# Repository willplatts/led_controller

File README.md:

# led_controller
LED array PCB for lighting with daisy chain controller

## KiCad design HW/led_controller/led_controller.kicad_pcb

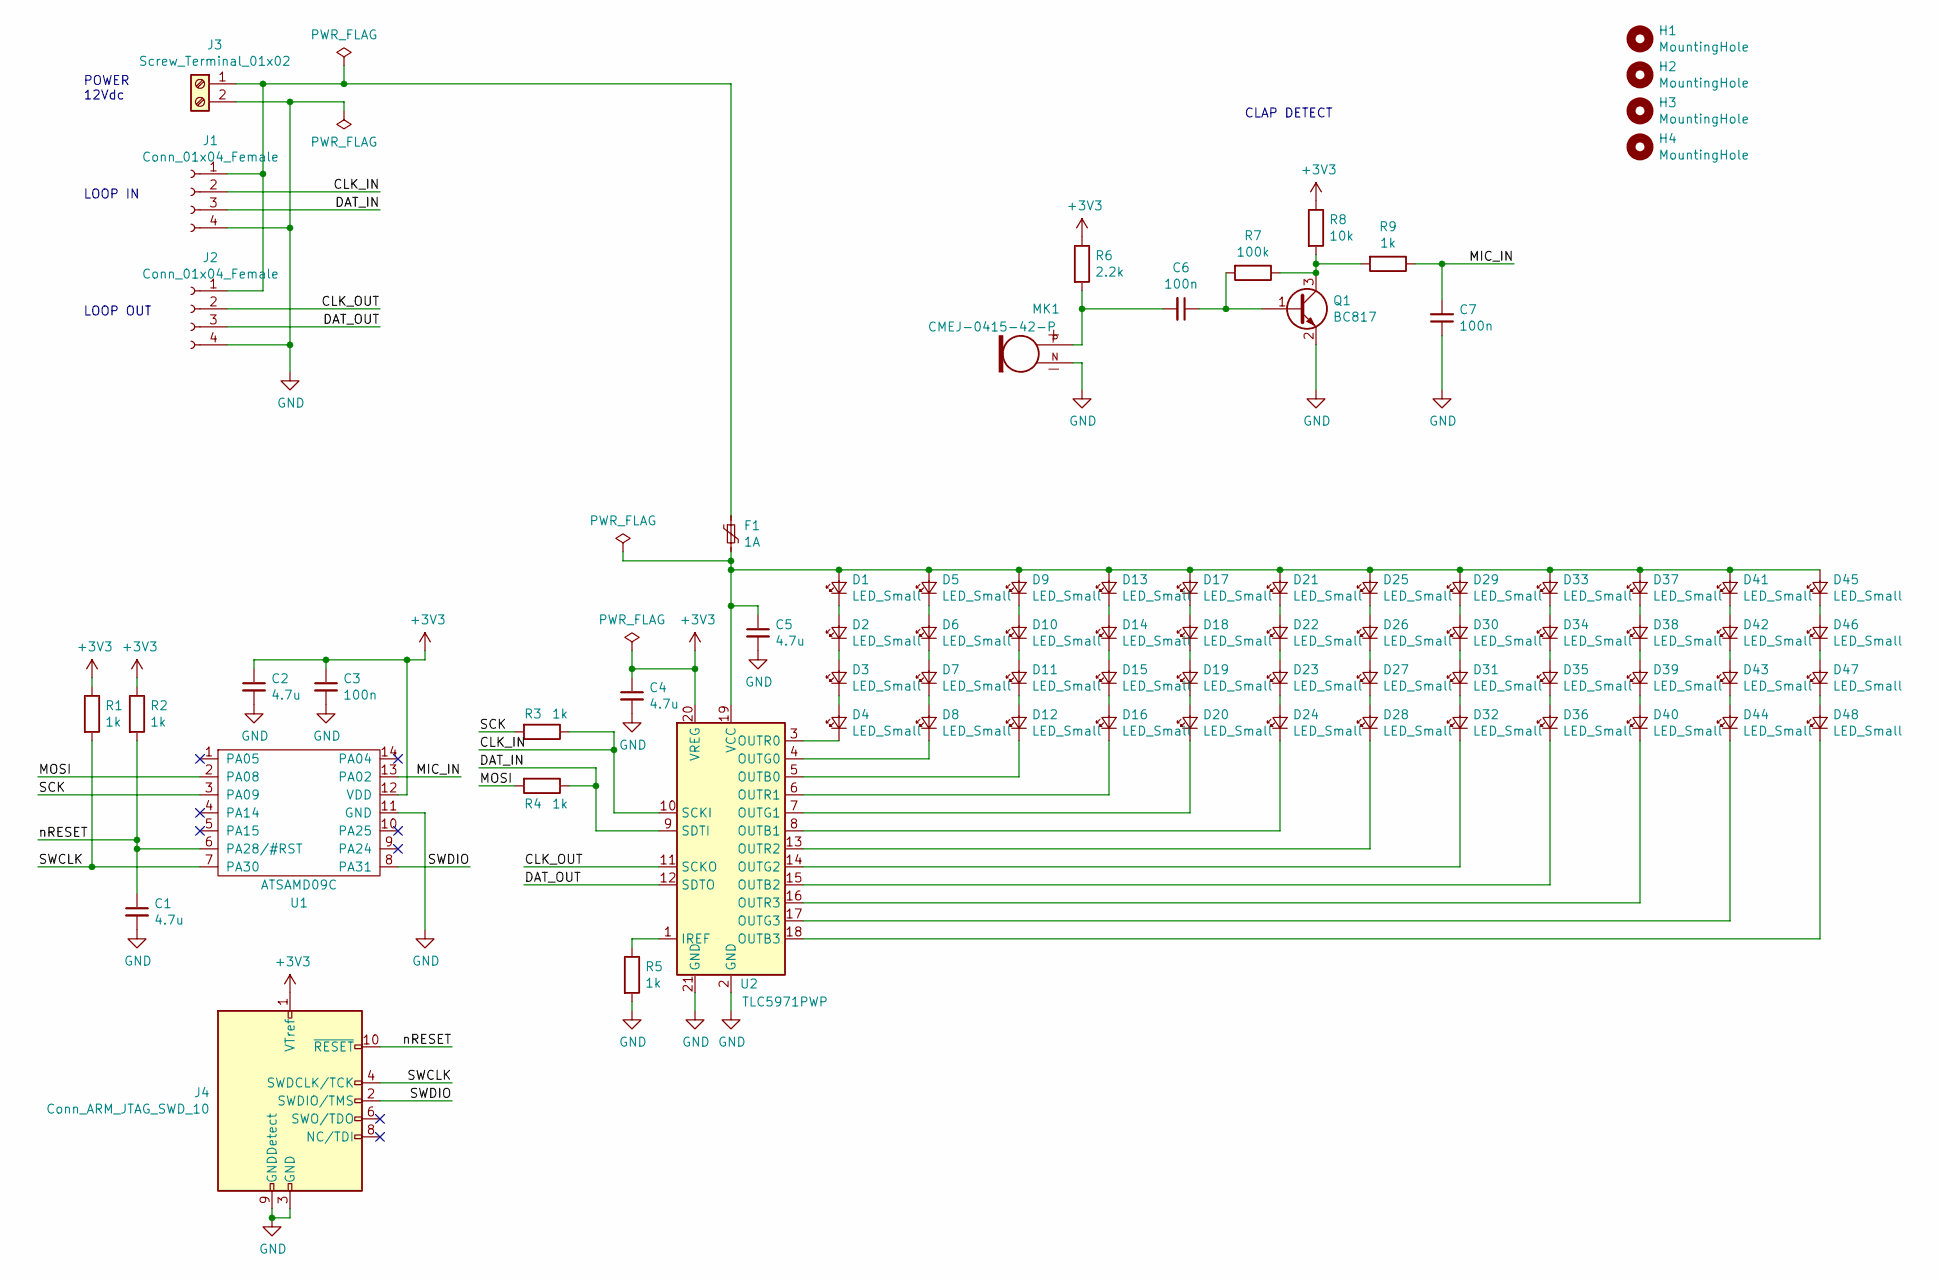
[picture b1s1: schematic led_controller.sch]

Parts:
C1, C2, C4, C5: 4.7u; C_1206_3216Metric_Pad1.42x1.75mm_HandSolder
C3, C6, C7: 100n; C_0603_1608Metric_Pad1.05x0.95mm_HandSolder
D1, D2, D3, D4, D5, D6, D7, D8, D9, D10, D11, D12, D13, D14, D15, D16, D17, D18, D19, D20, D21, D22, D23, D24, D25, D26, D27, D28, D29, D30, D31, D32, D33, D34, D35, D36, D37, D38, D39, D40, D41, D42, D43, D44, D45, D46, D47, D48: LED_Small; LED_PLCC_2835_Handsoldering
F1: 1A; R_1206_3216Metric_Pad1.42x1.75mm_HandSolder
H1, H2, H3, H4: MountingHole; MountingHole_3.2mm_M3
J1, J2: Conn_01x04_Female; PinHeader_1x04_P2.54mm_Vertical
J3: Screw_Terminal_01x02; TerminalBlock_Phoenix_MKDS-1,5-2_1x02_P5.00mm_Horizontal
J4: Conn_ARM_JTAG_SWD_10; PinHeader_2x05_P1.27mm_Vertical
MK1: CMEJ-0415-42-P; MIC_CMEJ-0415-42-P
Q1: BC817; SOT-23
R1, R2, R3, R4, R5, R9: 1k; R_0603_1608Metric_Pad1.05x0.95mm_HandSolder
R6: 2.2k; R_0603_1608Metric_Pad1.05x0.95mm_HandSolder
R7: 100k; R_0603_1608Metric_Pad1.05x0.95mm_HandSolder
R8: 10k; R_0603_1608Metric_Pad1.05x0.95mm_HandSolder
U1: ATSAMD09C; SOIC-14_3.9x8.7mm_P1.27mm
U2: TLC5971PWP; HTSSOP-20-1EP_4.4x6.5mm_P0.65mm_EP3.4x6.5mm_Mask2.75x3.43mm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

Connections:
+3V3: C2.1, C3.1, C4.1, J4.1 (VTref), R1.1, R2.1, R6.1, R8.1, U1.12 (VDD), U2.20 (VREG)
/CLK_IN: J1.2, R3.1, U2.10 (SCKI)
/CLK_OUT: J2.2, U2.11 (SCKO)
/DAT_IN: J1.3, R4.1, U2.9 (SDTI)
/DAT_OUT: J2.3, U2.12 (SDTO)
/MIC_IN: C7.2, R9.1, U1.13 (PA02)
/MOSI: R4.2, U1.2 (PA08)
/SCK: R3.2, U1.3 (PA09)
/SWCLK: J4.4 (SWDCLK/TCK), R1.2, U1.7 (PA30)
/SWDIO: J4.2 (SWDIO/TMS), U1.8 (PA31)
/nRESET: C1.1, J4.10 (~RESET~), R2.2, U1.6 (PA28/#RST)
GND: C1.2, C2.2, C3.2, C4.2, C5.2, C7.1, J1.4, J2.4, J3.2, J4.3 (GND), J4.5 (GND), J4.9 (GNDDetect), MK1.N (GND), Q1.2 (E), R5.2, U1.11 (GND), U2.2 (GND), U2.21 (GND)
unnamed: C5.1, D1.2 (A), D5.2 (A), D9.2 (A), D13.2 (A), D17.2 (A), D21.2 (A), D25.2 (A), D29.2 (A), D33.2 (A), D37.2 (A), D41.2 (A), D45.2 (A), F1.2, U2.19 (VCC)
unnamed: C6.1, Q1.1 (B), R7.2
unnamed: C6.2, MK1.P (OUTPUT), R6.2
unnamed: D1.1 (K), D2.2 (A)
unnamed: D2.1 (K), D3.2 (A)
unnamed: D3.1 (K), D4.2 (A)
unnamed: D4.1 (K), U2.3 (OUTR0)
unnamed: D5.1 (K), D6.2 (A)
unnamed: D6.1 (K), D7.2 (A)
unnamed: D7.1 (K), D8.2 (A)
unnamed: D8.1 (K), U2.4 (OUTG0)
unnamed: D10.1 (K), D11.2 (A)
unnamed: D9.1 (K), D10.2 (A)
unnamed: D11.1 (K), D12.2 (A)
unnamed: D12.1 (K), U2.5 (OUTB0)
unnamed: D13.1 (K), D14.2 (A)
unnamed: D14.1 (K), D15.2 (A)
unnamed: D15.1 (K), D16.2 (A)
unnamed: D16.1 (K), U2.6 (OUTR1)
unnamed: D17.1 (K), D18.2 (A)
unnamed: D18.1 (K), D19.2 (A)
unnamed: D19.1 (K), D20.2 (A)
unnamed: D20.1 (K), U2.7 (OUTG1)
unnamed: D21.1 (K), D22.2 (A)
unnamed: D22.1 (K), D23.2 (A)
unnamed: D23.1 (K), D24.2 (A)
unnamed: D24.1 (K), U2.8 (OUTB1)
unnamed: D25.1 (K), D26.2 (A)
unnamed: D26.1 (K), D27.2 (A)
unnamed: D27.1 (K), D28.2 (A)
unnamed: D28.1 (K), U2.13 (OUTR2)
unnamed: D29.1 (K), D30.2 (A)
unnamed: D30.1 (K), D31.2 (A)
unnamed: D31.1 (K), D32.2 (A)
unnamed: D32.1 (K), U2.14 (OUTG2)
unnamed: D33.1 (K), D34.2 (A)
unnamed: D34.1 (K), D35.2 (A)
unnamed: D35.1 (K), D36.2 (A)
unnamed: D36.1 (K), U2.15 (OUTB2)
unnamed: D37.1 (K), D38.2 (A)
unnamed: D38.1 (K), D39.2 (A)
unnamed: D39.1 (K), D40.2 (A)
unnamed: D40.1 (K), U2.16 (OUTR3)
unnamed: D41.1 (K), D42.2 (A)
unnamed: D42.1 (K), D43.2 (A)
unnamed: D43.1 (K), D44.2 (A)
unnamed: D44.1 (K), U2.17 (OUTG3)
unnamed: D45.1 (K), D46.2 (A)
unnamed: D46.1 (K), D47.2 (A)
unnamed: D47.1 (K), D48.2 (A)
unnamed: D48.1 (K), U2.18 (OUTB3)
unnamed: F1.1, J1.1, J2.1, J3.1
unnamed: Q1.3 (C), R7.1, R8.2, R9.2
unnamed: R5.1, U2.1 (IREF)

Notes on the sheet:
LOOP IN
LOOP OUT
POWER 12Vdc
CLAP DETECT

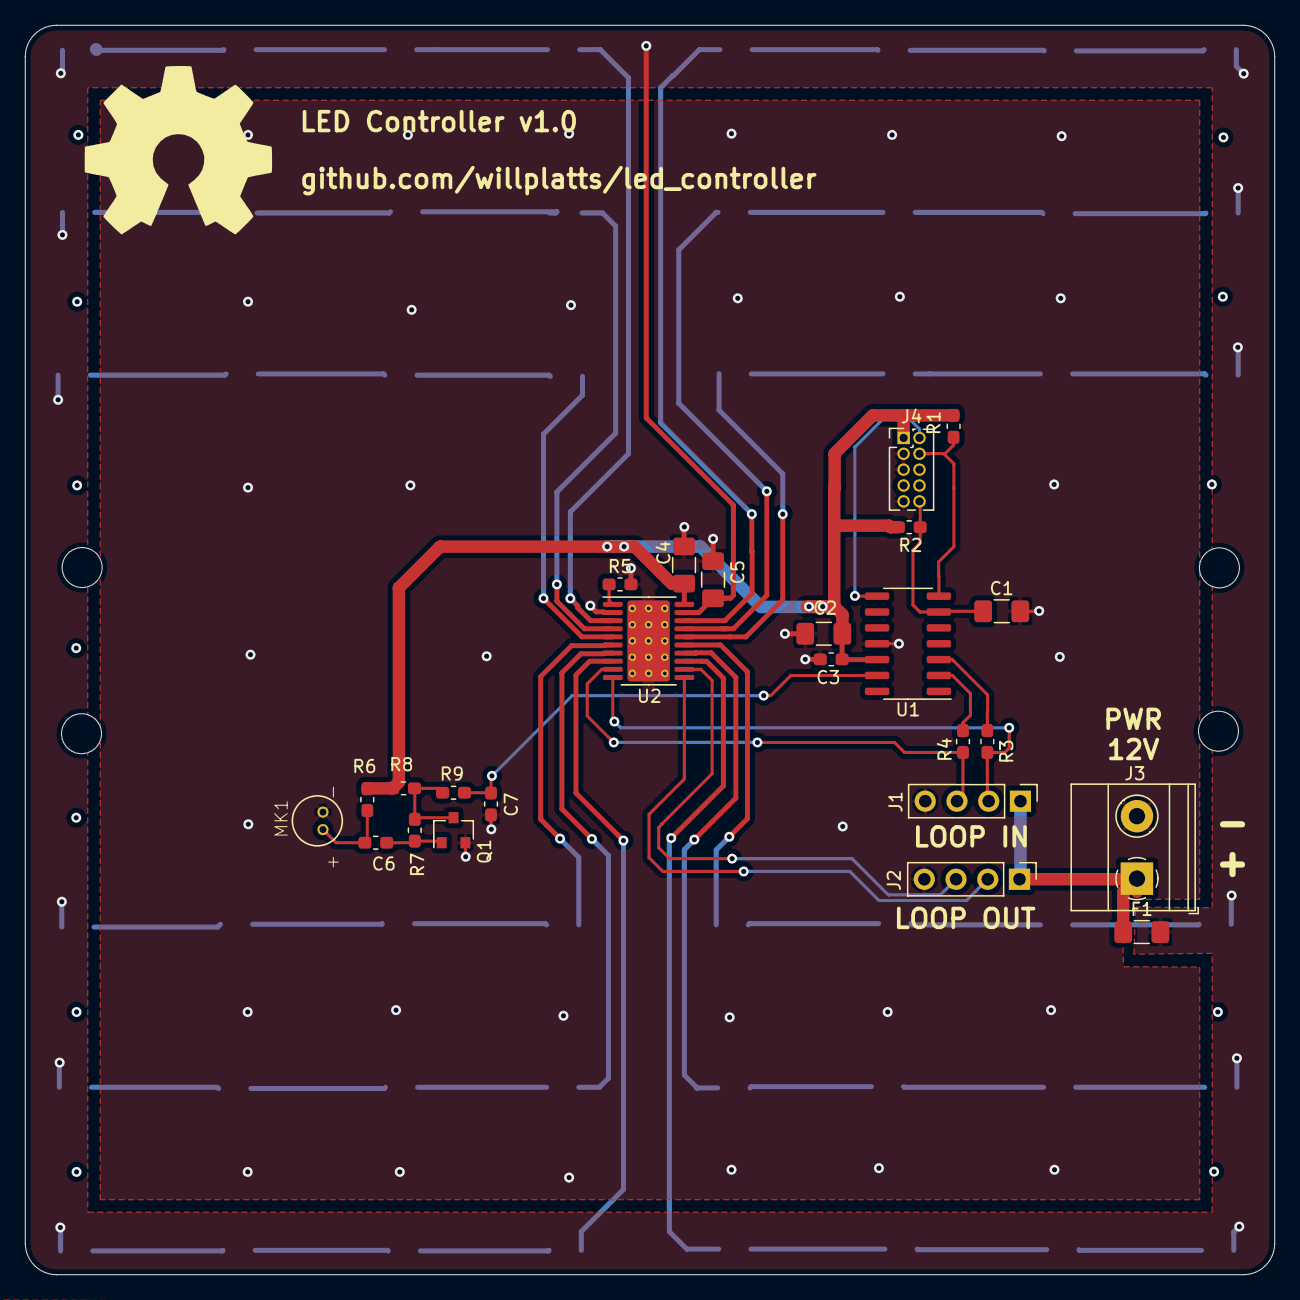
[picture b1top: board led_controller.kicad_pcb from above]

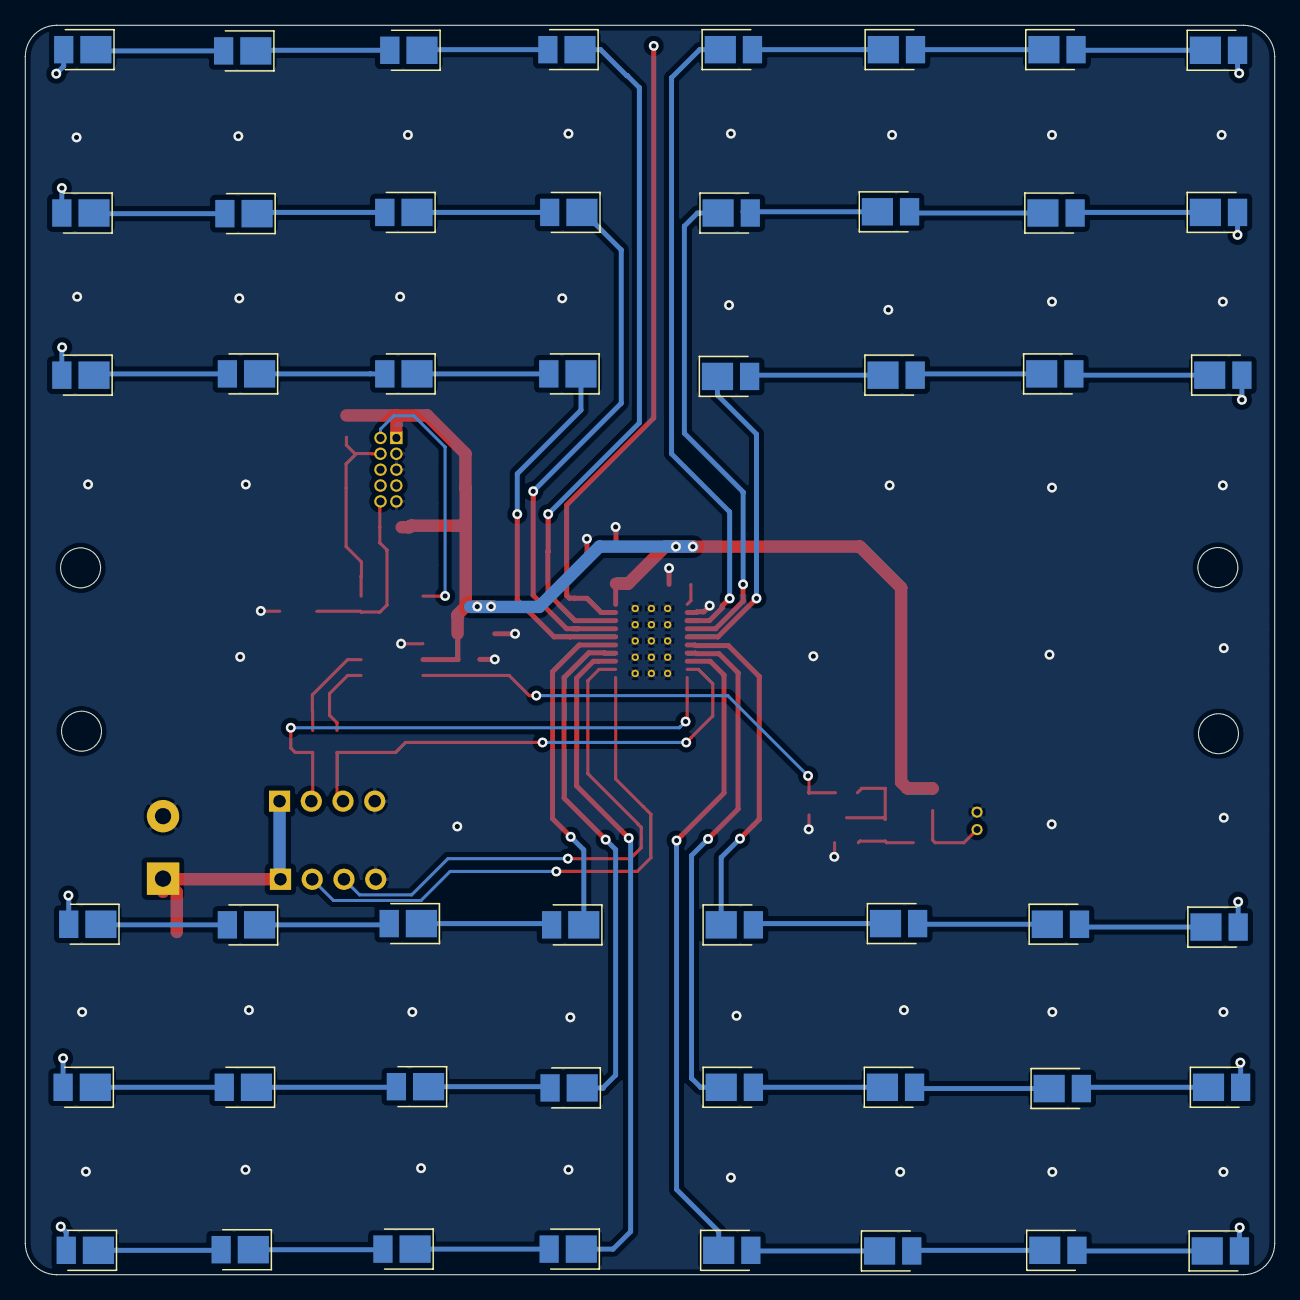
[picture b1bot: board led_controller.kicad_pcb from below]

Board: 2 copper layers, 100.0 x 100.0 mm, 77 parts (48 on the bottom side), 66 nets.

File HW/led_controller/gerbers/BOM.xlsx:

Ref | Value | Part | Manufacturer part no | Supplier | Qty
C1, C2, C4, C5 | 4.7u | Capacitor, 1206, 4.7uF, X5R, 25V | Generic | DIGI 1276-2880-1-ND | 4
C3, C6, C7 | 100n | Capacitor, 0603, 100nF, X7R, 50V | Generic | DIGI 1276-CL10B104KB8NNNLCT-ND | 3
D1-D48 | LED_Small | LED, white, 2835 | CREE JE2835AWT-00-0000-0B0A0UF840E | DIGI JE2835AWT-00-0000-0B0A0UF840ECT-ND | 48
F1 | 1A | Fuse, SMD 1206, 1A | BEL FUSE C1F 1 | DIGI 507-1878-1-ND | 1
J1, J2 | Conn_01x04_Female | Pin header, 2.54mm, 1x4 | TE 640454-4 | DIGI A19431-ND | 2
J3 | Screw_Terminal_01x02 | Screw terminal, 5mm, 1x2 | PHOENIX CONTACT 1935161 | DIGI 277-1667-ND | 1
J4 | Conn_ARM_JTAG_SWD_10 | Conn JTAG 2x5 | CNC TECH 3221-10-0100-00 | DIGI 1175-1733-ND | 1
MK1 | CMEJ-0415-42-P | Microphone, CMEJ-0415-42-P | CUI CMEJ-0415-42-P | DIGI 102-6542-ND | 1
Q1 | BC817 | Transistor, NPN, BC817, SOT-23 | ON SEMI BC817-16LT3G | DIGI BC817-16LT3GOSCT-ND | 1
R1-R5, R9 | 1k | Resistor, 0603, 1k | Generic | DIGI RHM1.0KDCT-ND | 6
R6 | 2.2k | Resistor, 0603, 2.2k | Generic | DIGI A130093CT-ND | 1
R7 | 100k | Resistor, 0603, 100k | Generic | DIGI CR0603-JW-104ELFCT-ND | 1
R8 | 10k | Resistor, 0603, 10k | Generic | DIGI RNCP0603FTD10K0CT-ND | 1
U1 | ATSAMD09C | MCU ATSAMD09C, SOIC-14 | MICROCHIP ATSAMD09C13A-SSUT | DIGI ATSAMD09C13A-SSUTCT-ND | 1
U2 | TLC5971PWP | LED Driver, HTSSOP-20 | TI TLC5971PWPR | DIGI 296-27796-1-ND | 1
DIGIKEY | https://www.digikey.co.uk/short/prp19m

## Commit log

2019-08-15 Adding PCB design so far
2019-08-15 Changing microphone to CMEJ-0415-42-P, mostly finished PCB, DRC passing, adding OSH logo and some text
2019-08-19 Completing PCB design, adding gerbers and PDF schematic
2019-08-27 Adding excel BOM
